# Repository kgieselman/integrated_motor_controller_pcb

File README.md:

# Integrated Motor Controller PCB

A reusable base board for yearly robotics competitions. The base board handles drive, sensing, control, and radio. Per-season expansion is exposed through a small set of discrete headers (AUX, UART, QWIIC I²C, servo), not a single dedicated mechanism connector.

Adapter boards are named after creature parts: **Fang** (ping pong gripper/launcher), with future adapters extending the menagerie.

## Architecture

```
┌──────────────────────────────────────────────────────────────────┐
│                        Base Board                                │
│                                                                  │
│  ┌───────────────────┐  ┌──────────────────────────────────────┐ │
│  │ Power             │  │  STM32 H563RIT6                      │ │
│  │ 2S/3S → 5V ×2     │  │  250 MHz, 2MB / 640KB                │ │
│  │ (aux + main)      │  │  Y1 ASE-25MHz active oscillator      │ │
│  │ 5V → 3.3V LDO     │  │  BZ buzzer, D6–D9 LEDs               │ │
│  │ USB/batt PowerPath|  └────────────┬─────────────────────────┘ │
│  └───────────────────┘               │                           │
│                                      │                           │
│  ┌───────────────────────────────────┼───────────────┐           │
│  │   DRV8874 ×2 Motor Drivers        │               │           │
│  │   ~9A peak each                   │  Encoders ×2  │           │
│  │   IN1/IN2 + IPROPI                │  TIM4 / TIM8  │           │
│  └───────────────────────────────────┴───────────────┘           │
│                                                                  │
│  Connectors (* = DNP, footprint reserved):                       │
│   J1  RCVR    1×4 pin       — ELRS/CRSF RX/TX + 5 V *            │
│   J2  SWD     2×3 pin       — SWDIO/SWCLK/nRST, 3.3 V *          │
│   J3  ENC 0   1×3 pin       — encoder 0 signal, 3.3 V *          │
│   J4  ENC 1   1×3 pin       — encoder 1 signal, 3.3 V *          │
│   J5  UART    1×3 pin       — expansion UART, JST GH 1.25 mm *   │
│   J6  CH0     1×3 pin       — servo 0, +5V_Aux, GND *            │
│   J7  I2C     1×4 pin       — I2C SDA/SCL, JST SH 1.0 mm *       │
│   J8  CH1     1×3 pin       — servo 1, +5V_Aux, GND *            │
│   J9  I2C     1×4 pin       — I2C SDA/SCL (alt), JST SH 1.0 mm * │
│   J10 CH2     1×3 pin       — servo 2, +5V_Aux, GND *            │
│   J11 USB-C   USB 2.0       — debug / VBUS-powered logic         │
│   J12 VMeter  1×2 pin       — +BATT/GND for external voltmeter * │
│   J13 BATT    XT60          — 2S/3S LiPo input *                 │
│   J14 MOT 0   1×2 pin       — motor 0 out, Molex Micro-Fit 3.0 * │
│   J15 MOT 1   1×2 pin       — motor 1 out, Molex Micro-Fit 3.0 * │
│   JP1/JP2     solder jumpers — CRSF RX path (bridged by design)  │
└──────────────────────────────────────────────────────────────────┘
```

## Key Specs

| | |
|---|---|
| **MCU** | STM32H563RIT6 — Cortex-M33 @ 250 MHz, 2 MB flash, 640 KB SRAM, LQFP-64 |
| **Clock** | Y1 ASE-25.000MHZ — Abracon active oscillator, 4-pin SMD 3.2×2.5 mm |
| **Motor drivers** | 2× DRV8874 (PWP-16, HTSSOP) — IN1/IN2 mode (PMODE driven high), IPROPI current sense |
| **IMU** | LSM6DSV (U6) — 6-axis, SPI1 on PB3/PB4/PB5, CS=PC12, INT1=PD2, INT2=PB8; LGA-14 3×2.5 mm |
| **EEPROM** | M24C64 — 64 Kbit, I²C1 on PB6/PB7, WC=PA9 |
| **RC control** | External CRSF/ELRS receiver via J1 (1×4); JP1/JP2 solder jumpers bridged by default |
| **Servo channels** | 3, powered from +5V_Aux buck |
| **Expansion UART** | JST GH 1.25 mm |
| **I2C expansion** | JST SH 1.0 mm, 1×4 |
| **Power input** | 2S/3S LiPo (7.4–12.6 V) via XT60; USB-C VBUS can power logic rails only |
| **Power topology** | SW1 power switch; SI7157DP; 2N7002; AP63205WU bucks (5V_Aux + 5V); AP1117-33 LDO for 3.3 V |
| **Debug** | SWD, MCU RST, MCU BOOT0, USR button, power switch, LEDs, buzzer |
| **Board** | 4-layer FR4 |

## Schematic Hierarchy

```
integrated_motor_controller.kicad_sch (Root)
├── power_regulator_2s_3s.kicad_sch — Battery input, power switch, bucks, LDO, VBAT sense
├── mcu_h563r.kicad_sch             — STM32H563, Y1 active oscillator, bypass, pin assignments, VCAP, SW2/SW3
├── motor_driver_drv8874.kicad_sch  — DRV8874 (instantiated twice: Motor 0 + Motor 1), motor output connectors
├── imu_lsm6dsv.kicad_sch           — LSM6DSV on SPI1
├── eeprom_m24c64.kicad_sch         — M24C64 on I²C1
├── debug_leds.kicad_sch            — Debug LEDs (×4), buzzer, user button, transistor drivers
└── connector_usb.kicad_sch         — USB-C receptacle + USBLC6-2SC6 ESD + CC pulldowns
```

Servo, encoder, UART, I2C, RCVR, and SWD connectors are placed directly on the root sheet.

## Status

- [x] Schematic hierarchy defined
- [x] Sub-schematics created and wired
- [x] PCB layout complete (KiCad 10)
- [x] Gerber / drill files generated (`gerbers/`)
- [x] ERC clean
- [x] DRC clean
- [x] BOM and pick-and-place outputs
- [ ] First board assembled and tested

## Getting Started

1. Clone this repo
2. Open `integrated_motor_controller.kicad_pro` in KiCad 10+
3. Custom symbols are in `libraries/symbols/` — resolved via the committed `sym-lib-table`
4. Custom footprints are in `libraries/footprints/` — resolved via `fp-lib-table`

## Repo Structure

```
integrated_motor_controller-pcb/
├── integrated_motor_controller.kicad_pro              # KiCad project file — open this
├── integrated_motor_controller.kicad_sch              # Root schematic
├── integrated_motor_controller.kicad_pcb              # PCB layout
├── power_regulator_2s_3s.kicad_sch
├── mcu_h563r.kicad_sch
├── motor_driver_drv8874.kicad_sch
├── imu_lsm6dsv.kicad_sch
├── eeprom_m24c64.kicad_sch
├── debug_leds.kicad_sch
├── connector_usb.kicad_sch
├── gerbers/                       # Gerber + drill files (ready for fab)
├── output/
│   ├── integrated_motor_controller.csv                # BOM export
│   └── integrated_motor_controller.net                # Netlist export
├── libraries/
│   ├── symbols/                   # Custom KiCad symbol libraries (.kicad_sym)
│   ├── footprints/                # Custom KiCad footprint libraries (.kicad_mod)
│   └── 3d_models/                 # STEP/WRL 3D models
├── sym-lib-table                  # Symbol library table (committed — paths are relative)
└── fp-lib-table                   # Footprint library table (committed — paths are relative)
```

## License

[CERN Open Hardware Licence Version 2 - Strongly Reciprocal (CERN-OHL-S-2.0)](LICENSE) © 2026 Kyle Gieselman

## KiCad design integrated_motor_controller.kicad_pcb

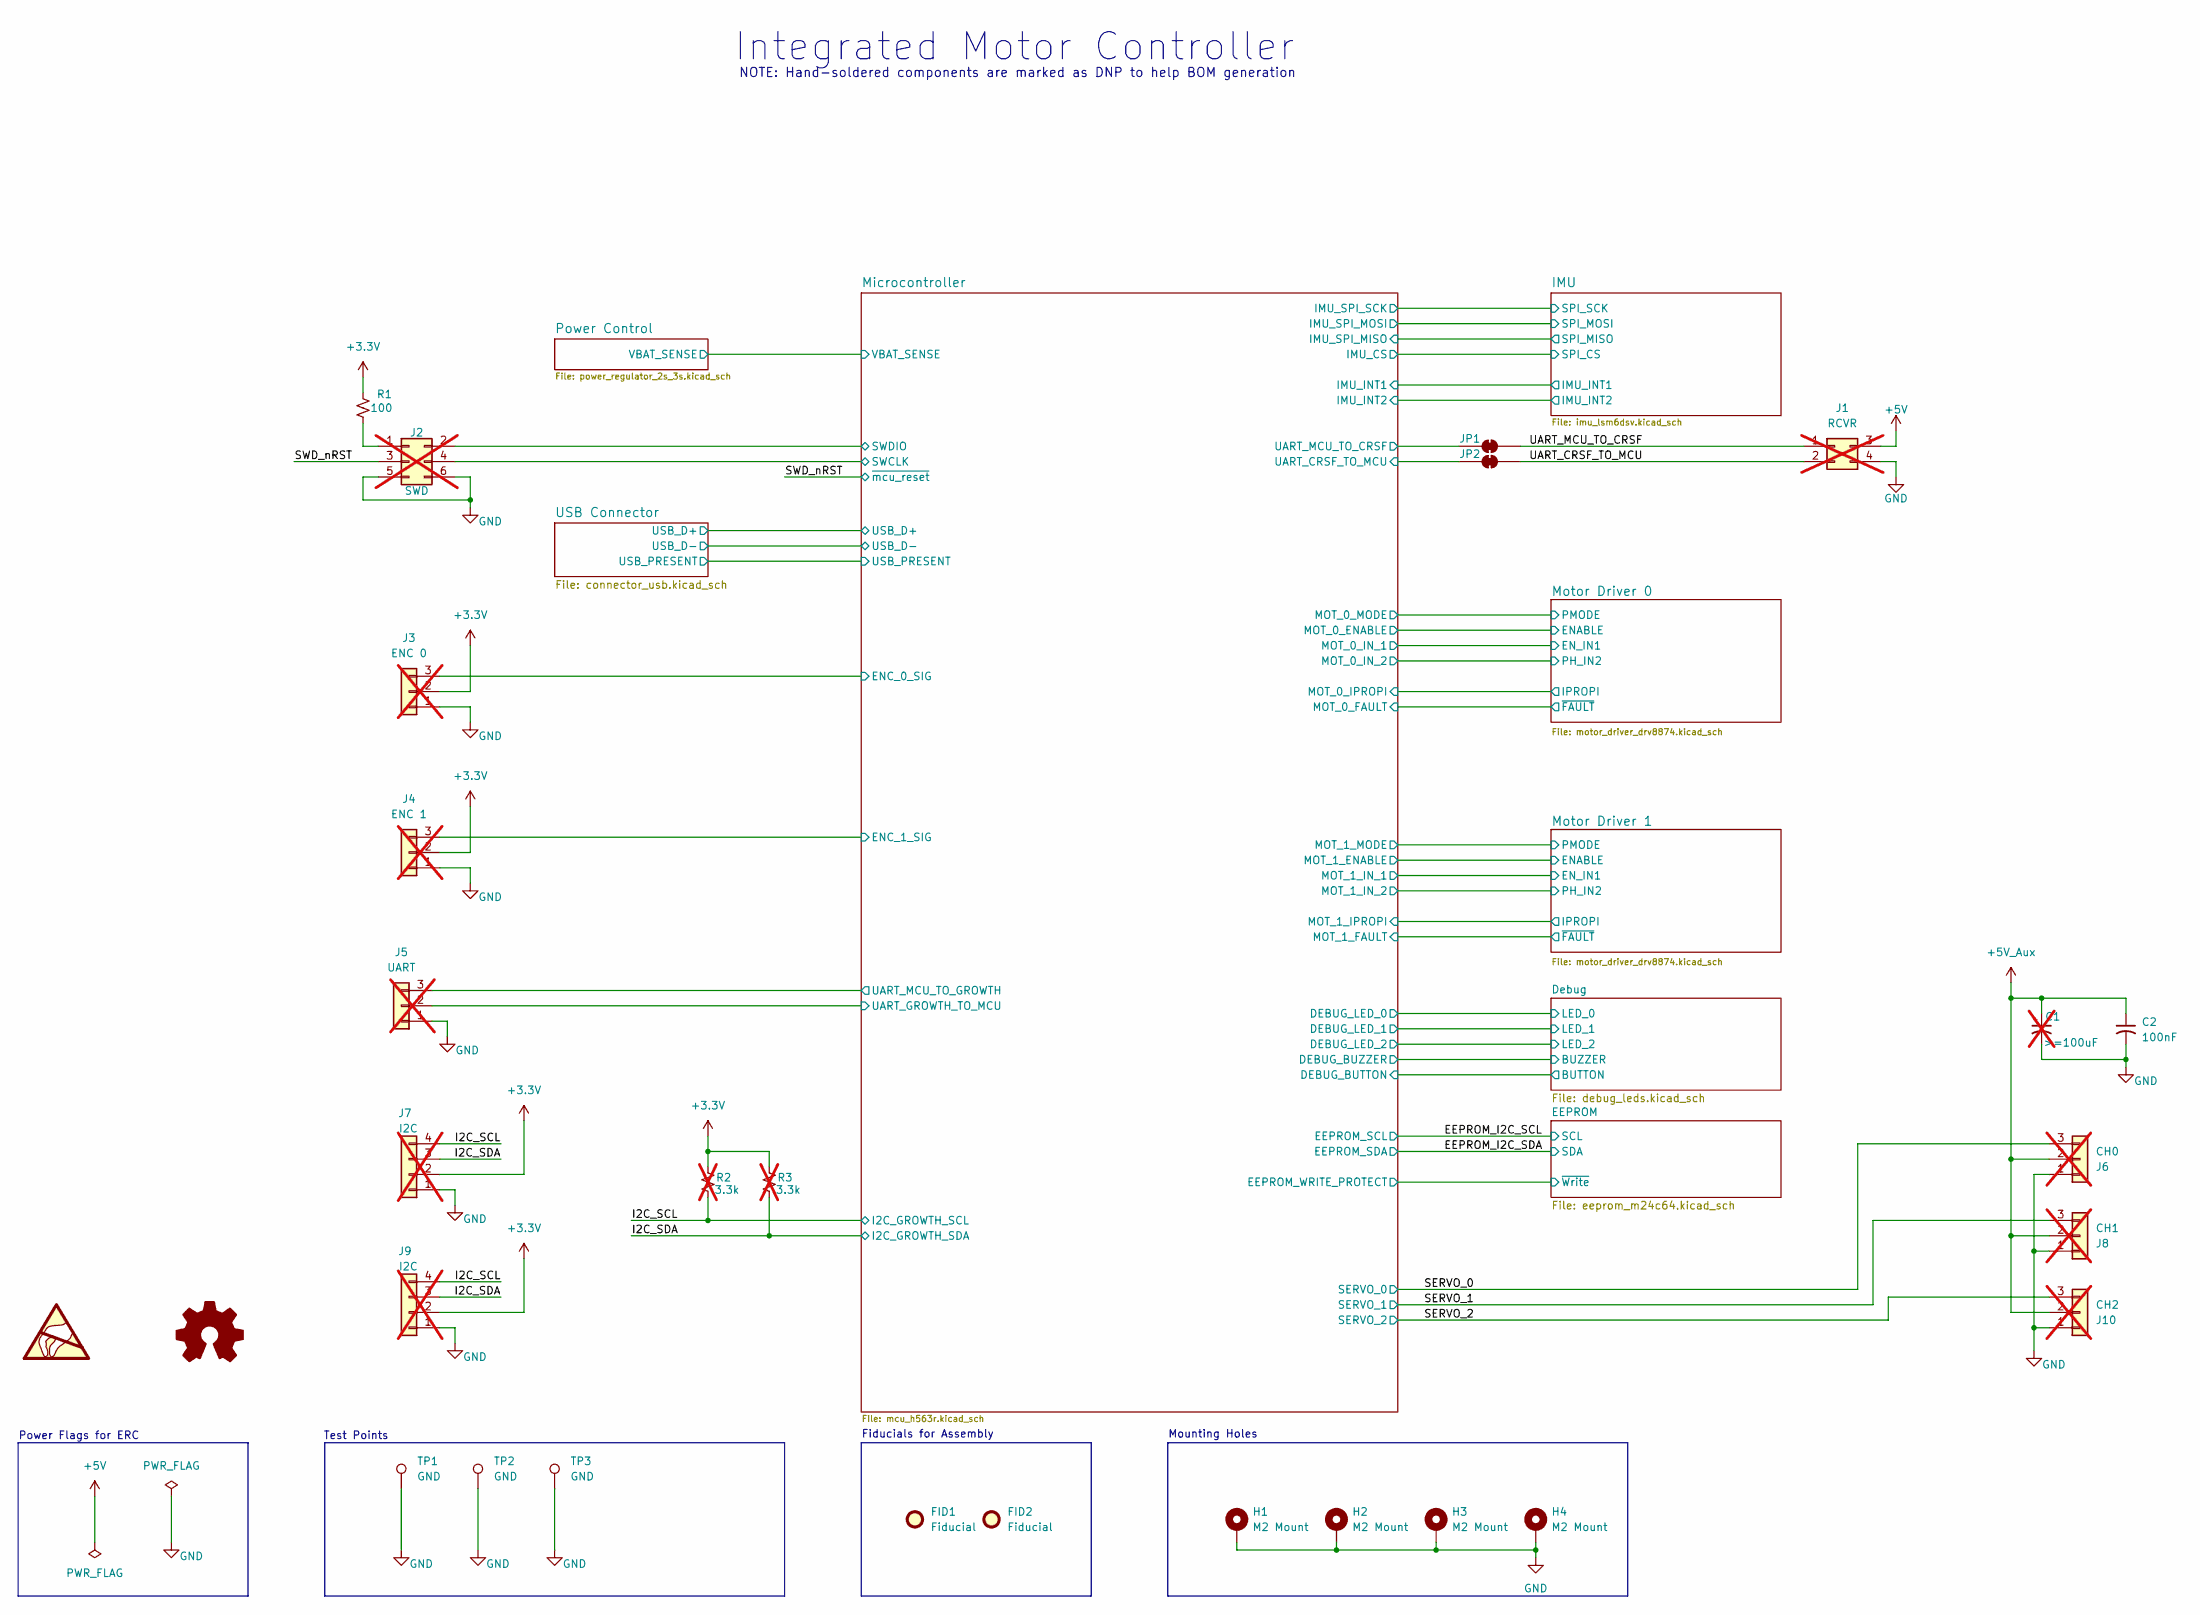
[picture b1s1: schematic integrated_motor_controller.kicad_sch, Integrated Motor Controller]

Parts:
C1: >=100uF; CP_Radial_D5.0mm_P2.00mm; Part No ---; JLCPCB ---; not fitted
C2: 100nF; C_0603_1608Metric; Part No CC0603KRX7R9BB104; JLCPCB C14663
FID1, FID2: Fiducial; ToolingHole_1.152mm; Part No ---; JLCPCB ---
H1, H2, H3, H4: M2 Mount; MountingHole_2.2mm_M2_Pad_Via; Part No ---; JLCPCB ---
J1: RCVR; PinHeader_1x04_P2.54mm_Vertical; Part No ---; JLCPCB ---; not fitted
J2: SWD; PinHeader_2x03_P2.54mm_Vertical; Part No ---; JLCPCB ---; not fitted
J3: ENC 0; PinHeader_1x03_P2.54mm_Vertical; Part No ---; JLCPCB ---; not fitted
J4: ENC 1; PinHeader_1x03_P2.54mm_Vertical; Part No ---; JLCPCB ---; not fitted
J5: UART; JST_GH_BM03B-GHS-TBT_1x03-1MP_P1.25mm_Vertical; Part No TODO; JLCPCB ---; not fitted
J6: CH0; PinHeader_1x03_P2.54mm_Vertical; Part No ----; JLCPCB ----; not fitted
J7, J9: I2C; JST_SH_BM04B-SRSS-TB_1x04-1MP_P1.00mm_Vertical; Part No TODO; JLCPCB ---; not fitted
J8: CH1; PinHeader_1x03_P2.54mm_Vertical; Part No ----; JLCPCB ----; not fitted
J10: CH2; PinHeader_1x03_P2.54mm_Vertical; Part No ----; JLCPCB ----; not fitted
JP1, JP2: SolderJumper_2_Bridged; SolderJumper-2_P1.3mm_Bridged_Pad1.0x1.5mm; Part No ---; JLCPCB ---
R1: 100; R_0603_1608Metric; Part No 0603WAF1000T5E; JLCPCB C22775
R2, R3: 3.3k; R_0603_1608Metric; Part No 0603WAF3301T5E; JLCPCB C22978; not fitted
SYM1: SYM_ESD_Large; ESD-Logo_6.6x6mm_SilkScreen; Part No ---; JLCPCB ---
SYM2: Logo_Open_Hardware_Small; KiCad-Logo2_6mm_SilkScreen; Part No ---; JLCPCB ---
TP1, TP2, TP3: GND; TestPoint_Pad_D1.0mm; Part No ---; JLCPCB ---

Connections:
+5V: J1.3; also elsewhere on the board
+5V_Aux: C1.1, C2.1, J6.2, J8.2, J10.2; also elsewhere on the board
/I2C_SCL: J7.4, J9.4, R2.1; also elsewhere on the board
/I2C_SDA: J7.3, J9.3, R3.1; also elsewhere on the board
/Microcontroller/ENC_0_SIG: J3.3; also elsewhere on the board
/Microcontroller/ENC_1_SIG: J4.3; also elsewhere on the board
/Microcontroller/SWCLK: J2.4; also elsewhere on the board
/Microcontroller/SWDIO: J2.2; also elsewhere on the board
/Microcontroller/UART_CRSF_TO_MCU: JP2.1 (A); also elsewhere on the board
/Microcontroller/UART_GROWTH_TO_MCU: J5.2; also elsewhere on the board
/Microcontroller/UART_MCU_TO_CRSF: JP1.1 (A); also elsewhere on the board
/Microcontroller/UART_MCU_TO_GROWTH: J5.3; also elsewhere on the board
/SERVO_0: J6.3; also elsewhere on the board
/SERVO_1: J8.3; also elsewhere on the board
/SERVO_2: J10.3; also elsewhere on the board
/SWD_nRST: J2.3; also elsewhere on the board
/UART_CRSF_TO_MCU: J1.2, JP2.2 (B)
/UART_MCU_TO_CRSF: J1.1, JP1.2 (B)
unnamed: J2.1, R1.2

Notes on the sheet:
Fiducials for Assembly
Test Points
Integrated Motor Controller
Power Flags for ERC
Mounting Holes
NOTE: Hand-soldered components are marked as DNP to help BOM generation

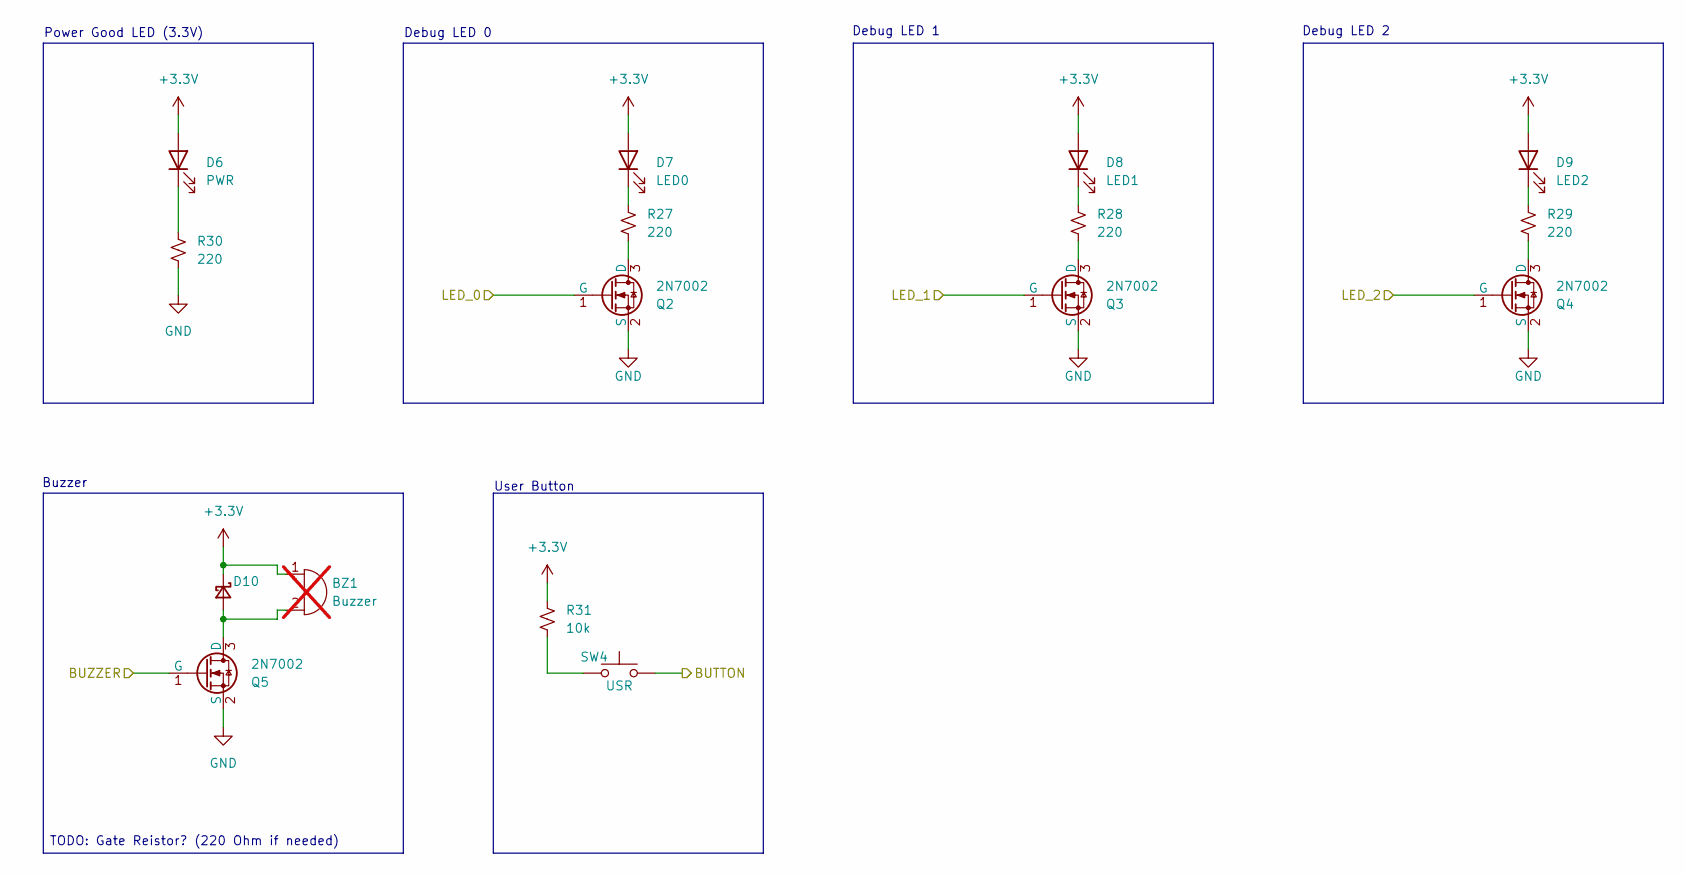
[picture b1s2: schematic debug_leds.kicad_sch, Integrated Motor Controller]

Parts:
BZ1: Buzzer; MagneticBuzzer_PUI_AT-0927-TT-6-R; Part No AT-0927-TT-6-R; JLCPCB ---; not fitted
D6: PWR; LED_0603_1608Metric; Part No KT-0603R; JLCPCB C2286
D7: LED0; LED_0603_1608Metric; Part No KT-0603R; JLCPCB C2286
D8: LED1; LED_0603_1608Metric; Part No KT-0603R; JLCPCB C2286
D9: LED2; LED_0603_1608Metric; Part No KT-0603R; JLCPCB C2286
D10: Schottky; D_SOD-123; Part No B5819W SL; JLCPCB C8598
Q2, Q3, Q4, Q5: 2N7002; SOT-23; Part No 2N7002; JLCPCB C8545
R27, R28, R29, R30: 220; R_0603_1608Metric; Part No 0603WAF2200T5E; JLCPCB C22962
R31: 10k; R_0603_1608Metric; Part No 0603WAF1002T5E; JLCPCB C25804
SW4: USR; SW_SPST_TS-1088-xR020; Part No TS-1088-AR02016; JLCPCB C720477

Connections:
/Debug/BUTTON: SW4.2; also elsewhere on the board
/Debug/BUZZER: Q5.1 (G); also elsewhere on the board
/Debug/LED_0: Q2.1 (G); also elsewhere on the board
/Debug/LED_1: Q3.1 (G); also elsewhere on the board
/Debug/LED_2: Q4.1 (G); also elsewhere on the board
unnamed: BZ1.2 (-), D10.2 (A), Q5.3 (D)
unnamed: D7.1 (K), R27.1
unnamed: D8.1 (K), R28.1
unnamed: Q2.3 (D), R27.2
unnamed: Q3.3 (D), R28.2
unnamed: R31.1, SW4.1

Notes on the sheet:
Debug LED 2
Buzzer
User Button
Debug LED 0
Power Good LED (3.3V)
Debug LED 1
TODO: Gate Reistor? (220 Ohm if needed)

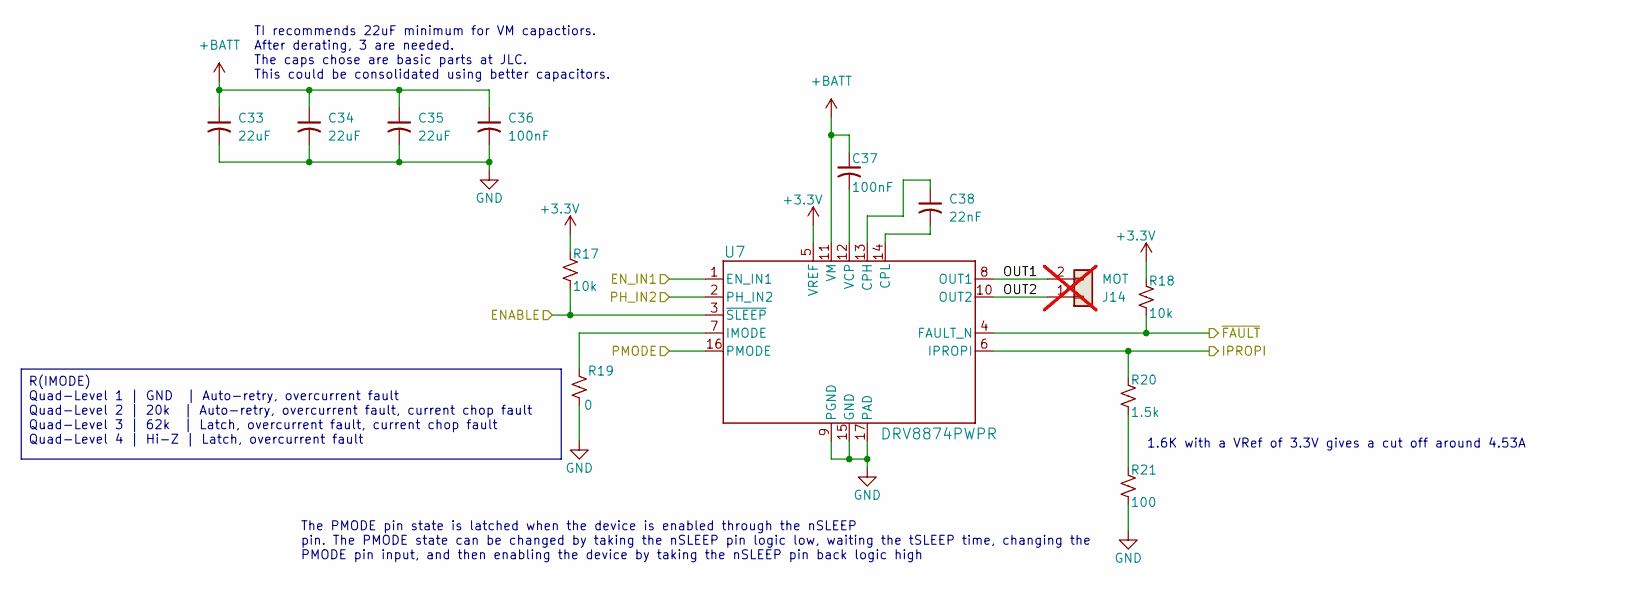
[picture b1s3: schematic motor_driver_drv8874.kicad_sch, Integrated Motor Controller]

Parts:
C33, C34, C35: 22uF; C_1206_3216Metric; Part No CL31A226KAHNNNE; JLCPCB C12891
C36, C37: 100nF; C_0603_1608Metric; Part No CC0603KRX7R9BB104; JLCPCB C14663
C38: 22nF; C_0603_1608Metric; Part No CL10B223KB8NNNC; JLCPCB C21122
J14: MOT; Molex_Micro-Fit_3.0_43650-0215_1x02_P3.00mm_Vertical; Part No 0436500215; JLCPCB ---; not fitted
R17, R18: 10k; R_0603_1608Metric; Part No 0603WAF1002T5E; JLCPCB C25804
R19: 0; R_0805_2012Metric; Part No 0805W8F0000T5E; JLCPCB C17477
R20: 1.5k; R_0805_2012Metric; Part No 0805W8F1501T5E; JLCPCB C4310
R21: 100; R_0805_2012Metric; Part No 0805W8F1000T5E; JLCPCB C17408
U7: DRV8874PWPR; PWP0016J_N; Part No DRV8874PWPR; JLCPCB C1855818

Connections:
+BATT: C33.1, C34.1, C35.1, C36.1, C37.1, U7.11 (VM); also elsewhere on the board
/Microcontroller/MOT_0_ENABLE: R17.1, U7.3 (~SLEEP); also elsewhere on the board
/Microcontroller/MOT_0_FAULT: R18.1, U7.4 (FAULT_N); also elsewhere on the board
/Microcontroller/MOT_0_IN_1: U7.1 (EN_IN1); also elsewhere on the board
/Microcontroller/MOT_0_IN_2: U7.2 (PH_IN2); also elsewhere on the board
/Microcontroller/MOT_0_IPROPI: R20.2, U7.6 (IPROPI); also elsewhere on the board
/Microcontroller/MOT_0_MODE: U7.16 (PMODE); also elsewhere on the board
/Motor Driver 0/OUT1: J14.2, U7.8 (OUT1)
/Motor Driver 0/OUT2: J14.1, U7.10 (OUT2)
unnamed: R20.1, R21.2
unnamed: C38.1, U7.13 (CPH)
unnamed: C38.2, U7.14 (CPL)
unnamed: R19.1, U7.7 (IMODE)
unnamed: C37.2, U7.12 (VCP)

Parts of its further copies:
C39, C40, C41: 22uF; C_1206_3216Metric; Part No CL31A226KAHNNNE; JLCPCB C12891
C42, C43: 100nF; C_0603_1608Metric; Part No CC0603KRX7R9BB104; JLCPCB C14663
C44: 22nF; C_0603_1608Metric; Part No CL10B223KB8NNNC; JLCPCB C21122
J15: MOT; Molex_Micro-Fit_3.0_43650-0215_1x02_P3.00mm_Vertical; Part No 0436500215; JLCPCB ---; not fitted
R22, R23: 10k; R_0603_1608Metric; Part No 0603WAF1002T5E; JLCPCB C25804
R24: 0; R_0805_2012Metric; Part No 0805W8F0000T5E; JLCPCB C17477
R25: 1.5k; R_0805_2012Metric; Part No 0805W8F1501T5E; JLCPCB C4310
R26: 100; R_0805_2012Metric; Part No 0805W8F1000T5E; JLCPCB C17408
U8: DRV8874PWPR; PWP0016J_N; Part No DRV8874PWPR; JLCPCB C1855818

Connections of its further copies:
+BATT: C39.1, C40.1, C41.1, C42.1, C43.1, U8.11 (VM); also elsewhere on the board
/Microcontroller/MOT_1_ENABLE: R22.1, U8.3 (~SLEEP); also elsewhere on the board
/Microcontroller/MOT_1_FAULT: R23.1, U8.4 (FAULT_N); also elsewhere on the board
/Microcontroller/MOT_1_IN_1: U8.1 (EN_IN1); also elsewhere on the board
/Microcontroller/MOT_1_IN_2: U8.2 (PH_IN2); also elsewhere on the board
/Microcontroller/MOT_1_IPROPI: R25.2, U8.6 (IPROPI); also elsewhere on the board
/Microcontroller/MOT_1_MODE: U8.16 (PMODE); also elsewhere on the board
/Motor Driver 1/OUT1: J15.2, U8.8 (OUT1)
/Motor Driver 1/OUT2: J15.1, U8.10 (OUT2)
unnamed: R25.1, R26.2
unnamed: C44.1, U8.13 (CPH)
unnamed: C44.2, U8.14 (CPL)
unnamed: R24.1, U8.7 (IMODE)
unnamed: C43.2, U8.12 (VCP)

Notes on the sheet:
1.6K with a VRef of 3.3V gives a cut off around 4.53A
The PMODE pin state is latched when the device is enabled through the nSLEEP pin. The PMODE state can be changed by taking the nSLEEP pin logic low, waiting the tSLEEP time, changing the PMODE pin input, and then enabling the device by taking the nSLEEP pin back logic high
TI recommends 22uF minimum for VM capactiors. After derating, 3 are needed. The caps chose are basic parts at JLC. This could be consolidated using better capacitors.
R(IMODE) Quad-Level 1 | GND | Auto-retry, overcurrent fault Quad-Level 2 | 20k | Auto-retry, overcurrent fault, current chop fault Quad-Level 3 | 62k | Latch, overcurrent fault, current chop fault Quad-Level 4 | Hi-Z | Latch, overcurrent fault

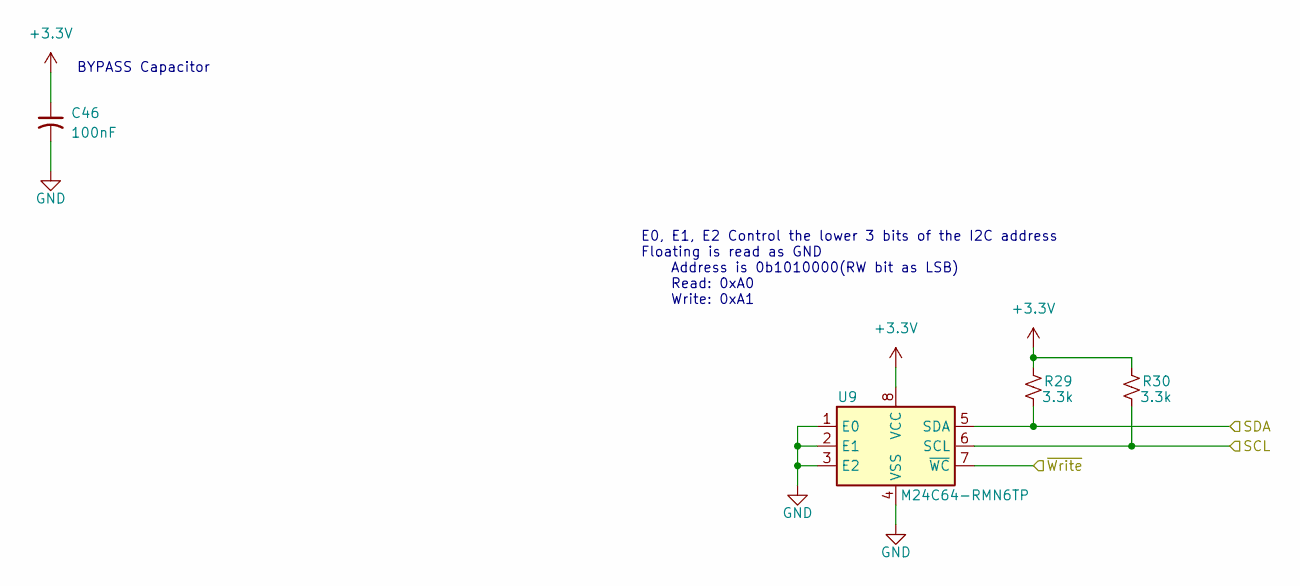
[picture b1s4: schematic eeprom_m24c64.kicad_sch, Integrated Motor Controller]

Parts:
C46: 100nF; C_0603_1608Metric; Part No CC0603KRX7R9BB104; JLCPCB C14663
R29, R30: 3.3k; R_0603_1608Metric; Part No 0603WAF3301T5E; JLCPCB C22978
U9: M24C64-RMN6TP; SOIC-8_3.9x4.9mm_P1.27mm; Part No M24C64-RMN6TP; JLCPCB C79988

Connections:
/EEPROM/~Write: U9.7 (~WC); also elsewhere on the board

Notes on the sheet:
E0, E1, E2 Control the lower 3 bits of the I2C address Floating is read as GND Address is 0b1010000(RW bit as LSB) Read: 0xA0 Write: 0xA1
BYPASS Capacitor

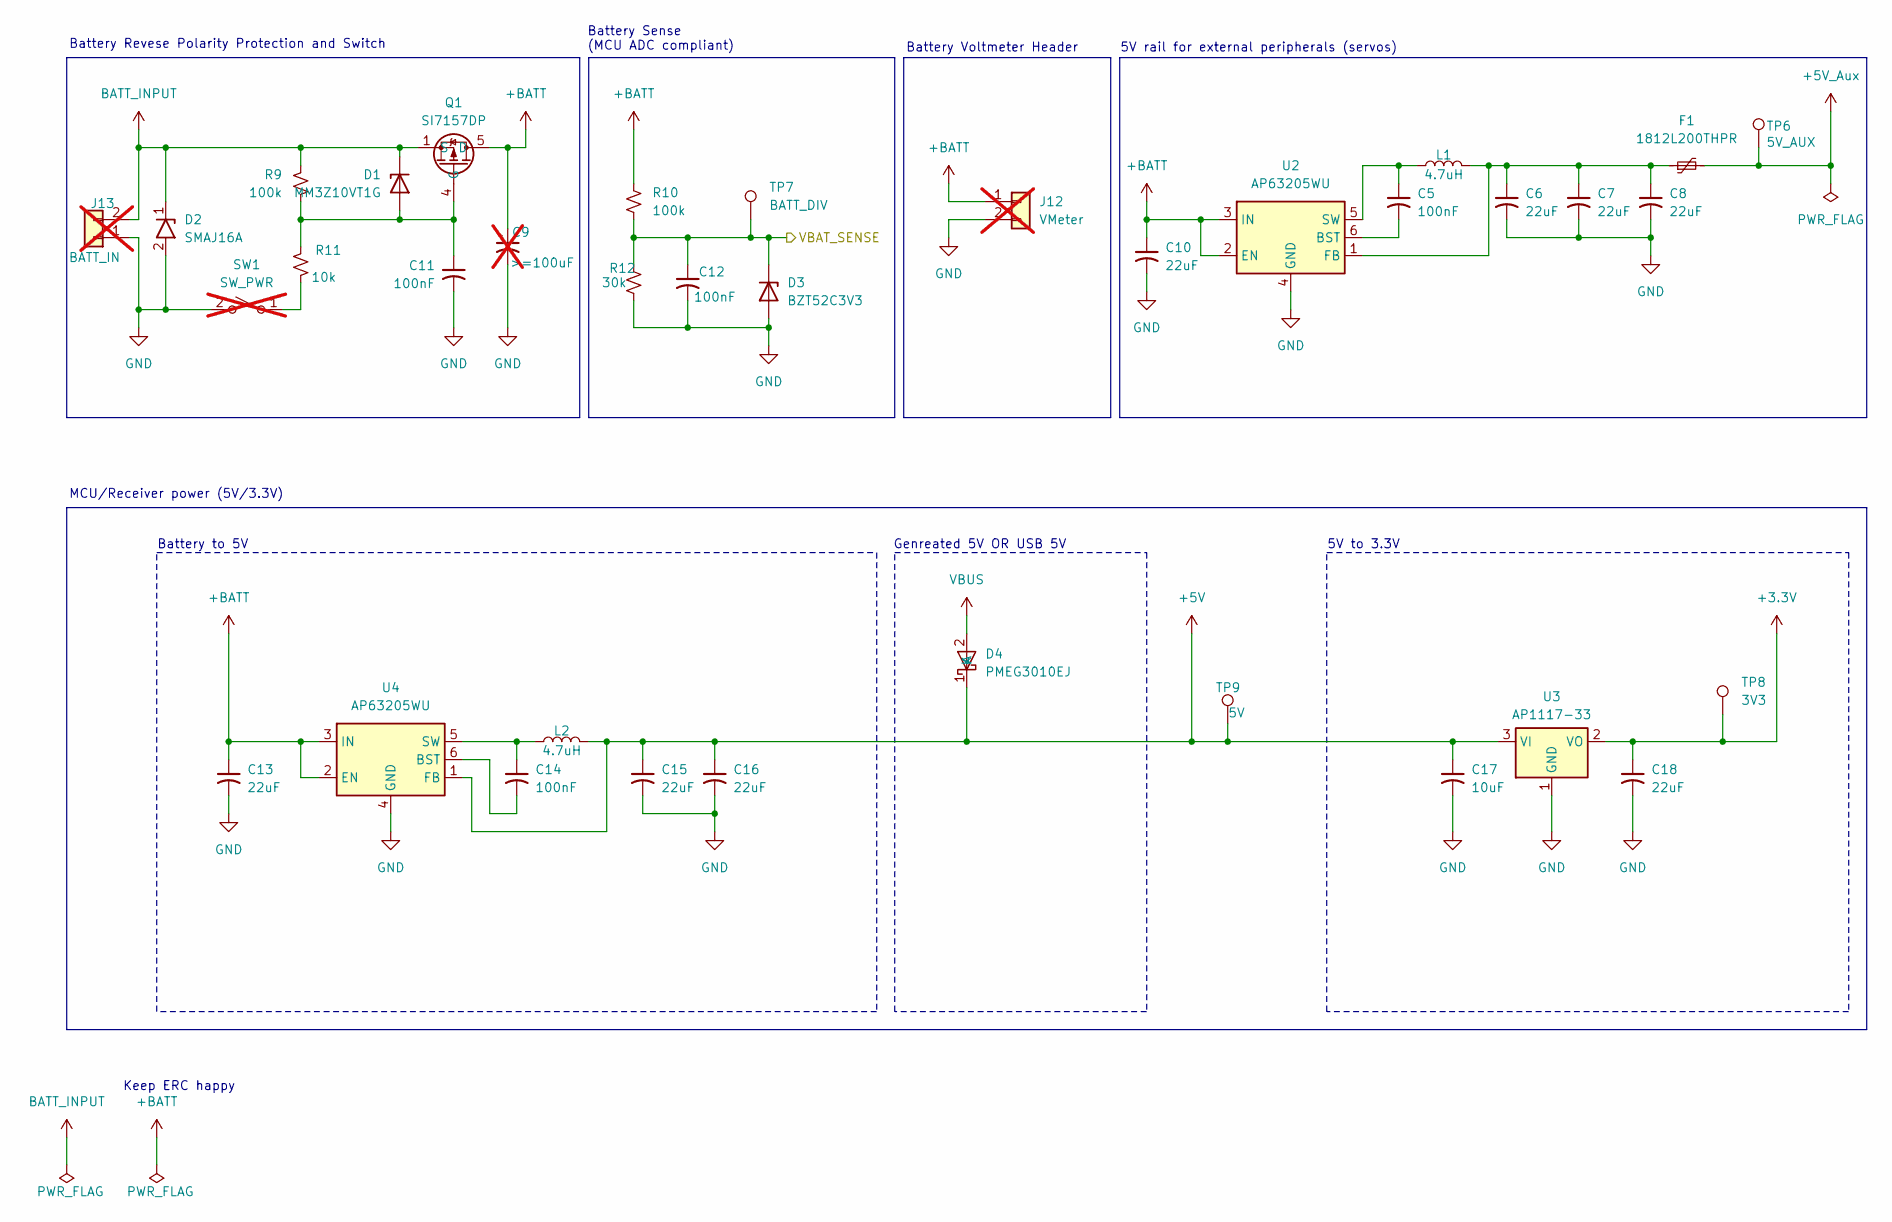
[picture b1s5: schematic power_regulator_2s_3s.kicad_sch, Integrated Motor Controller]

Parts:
C5, C11, C12, C14: 100nF; C_0603_1608Metric; Part No CC0603KRX7R9BB104; JLCPCB C14663
C6, C7, C8, C10, C13, C15, C16, C18: 22uF; C_1206_3216Metric; Part No CL31A226KAHNNNE; JLCPCB C12891
C9: >=100uF; CP_Radial_D5.0mm_P2.00mm; Part No ---; JLCPCB ---; not fitted
C17: 10uF; C_0603_1608Metric; Part No CL10A106MA8NRNC; JLCPCB C96446
D1: MM3Z10VT1G; D_SOD-323; Part No MM3Z10VT1G; JLCPCB C39057
D2: SMAJ16A; D_SMA; Part No SMAJ16A; JLCPCB C74561
D3: BZT52C3V3; D_SOD-123; Part No BZT52C3V3-7-F; JLCPCB C151564
D4: PMEG3010EJ; D_SOD-323F; Part No PMEG3010EJ,115; JLCPCB C255586
F1: 1812L200THPR; Fuse_1812_4532Metric; Part No 1812L200THPR; JLCPCB C207074
J12: VMeter; PinHeader_1x02_P2.54mm_Vertical; Part No ---; JLCPCB ---; not fitted
J13: BATT_IN; AMASS_XT60-M_1x02_P7.20mm_Vertical; Part No ---; JLCPCB ---; not fitted
L1, L2: 4.7uH; L_Sunlord_MWSA0503S; Part No MWSA0503S-4R7MT; JLCPCB C408410
Q1: SI7157DP; PowerPAK_SO-8_Single; Part No SI7157DP-T1-GE3; JLCPCB C3279562
R9, R10: 100k; R_0603_1608Metric; Part No 0603WAF1003T5E; JLCPCB C25803
R11: 10k; R_0603_1608Metric; Part No 0603WAF1002T5E; JLCPCB C25804
R12: 30k; R_0603_1608Metric; Part No 0603WAF3002T5E; JLCPCB C22984
SW1: SW_PWR; PinHeader_1x02_P2.54mm_Vertical; Part No ---; JLCPCB ---; not fitted
TP6: 5V_AUX; TestPoint_Pad_D1.0mm; Part No ---; JLCPCB ---
TP7: BATT_DIV; TestPoint_Pad_D1.0mm; Part No ---; JLCPCB ---
TP8: 3V3; TestPoint_Pad_D1.0mm; Part No ---; JLCPCB ---
TP9: 5V; TestPoint_Pad_D1.0mm; Part No ---; JLCPCB ---
U2, U4: AP63205WU; TSOT-23-6; Part No AP63205WU-7; JLCPCB C2071056
U3: AP1117-33; SOT-223-3_TabPin2; Part No AMS1117-3.3; JLCPCB C6186

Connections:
+5V: C15.1, C16.1, C17.1, D4.1 (K), L2.2, TP9.1 (1_1), U3.3 (VI), U4.1 (FB); also elsewhere on the board
+5V_Aux: F1.2, TP6.1 (1_1); also elsewhere on the board
+BATT: C9.1, C10.1, C13.1, J12.1, Q1.5 (D), R10.1, U2.2 (EN), U2.3 (IN), U4.2 (EN), U4.3 (IN); also elsewhere on the board
/Microcontroller/VBAT_SENSE: C12.1, D3.1 (K), R10.2, R12.1, TP7.1 (1_1); also elsewhere on the board
BATT_INPUT: D1.1 (K), D2.1 (A1), J13.2, Q1.1 (S), Q1.2 (S), Q1.3 (S), R9.2
unnamed: C11.1, D1.2 (A), Q1.4 (G), R9.1, R11.2
unnamed: R11.1, SW1.1 (A)
unnamed: C5.2, U2.6 (BST)
unnamed: C6.1, C7.1, C8.1, F1.1, L1.2, U2.1 (FB)
unnamed: C5.1, L1.1, U2.5 (SW)
unnamed: C14.2, U4.6 (BST)
unnamed: C14.1, L2.1, U4.5 (SW)
VBUS: D4.2 (A); also elsewhere on the board

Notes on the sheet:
Battery to 5V
Battery Sense (MCU ADC compliant)
Battery Revese Polarity Protection and Switch
Battery Voltmeter Header
5V to 3.3V
MCU/Receiver power (5V/3.3V)
Keep ERC happy
Genreated 5V OR USB 5V
5V rail for external peripherals (servos)

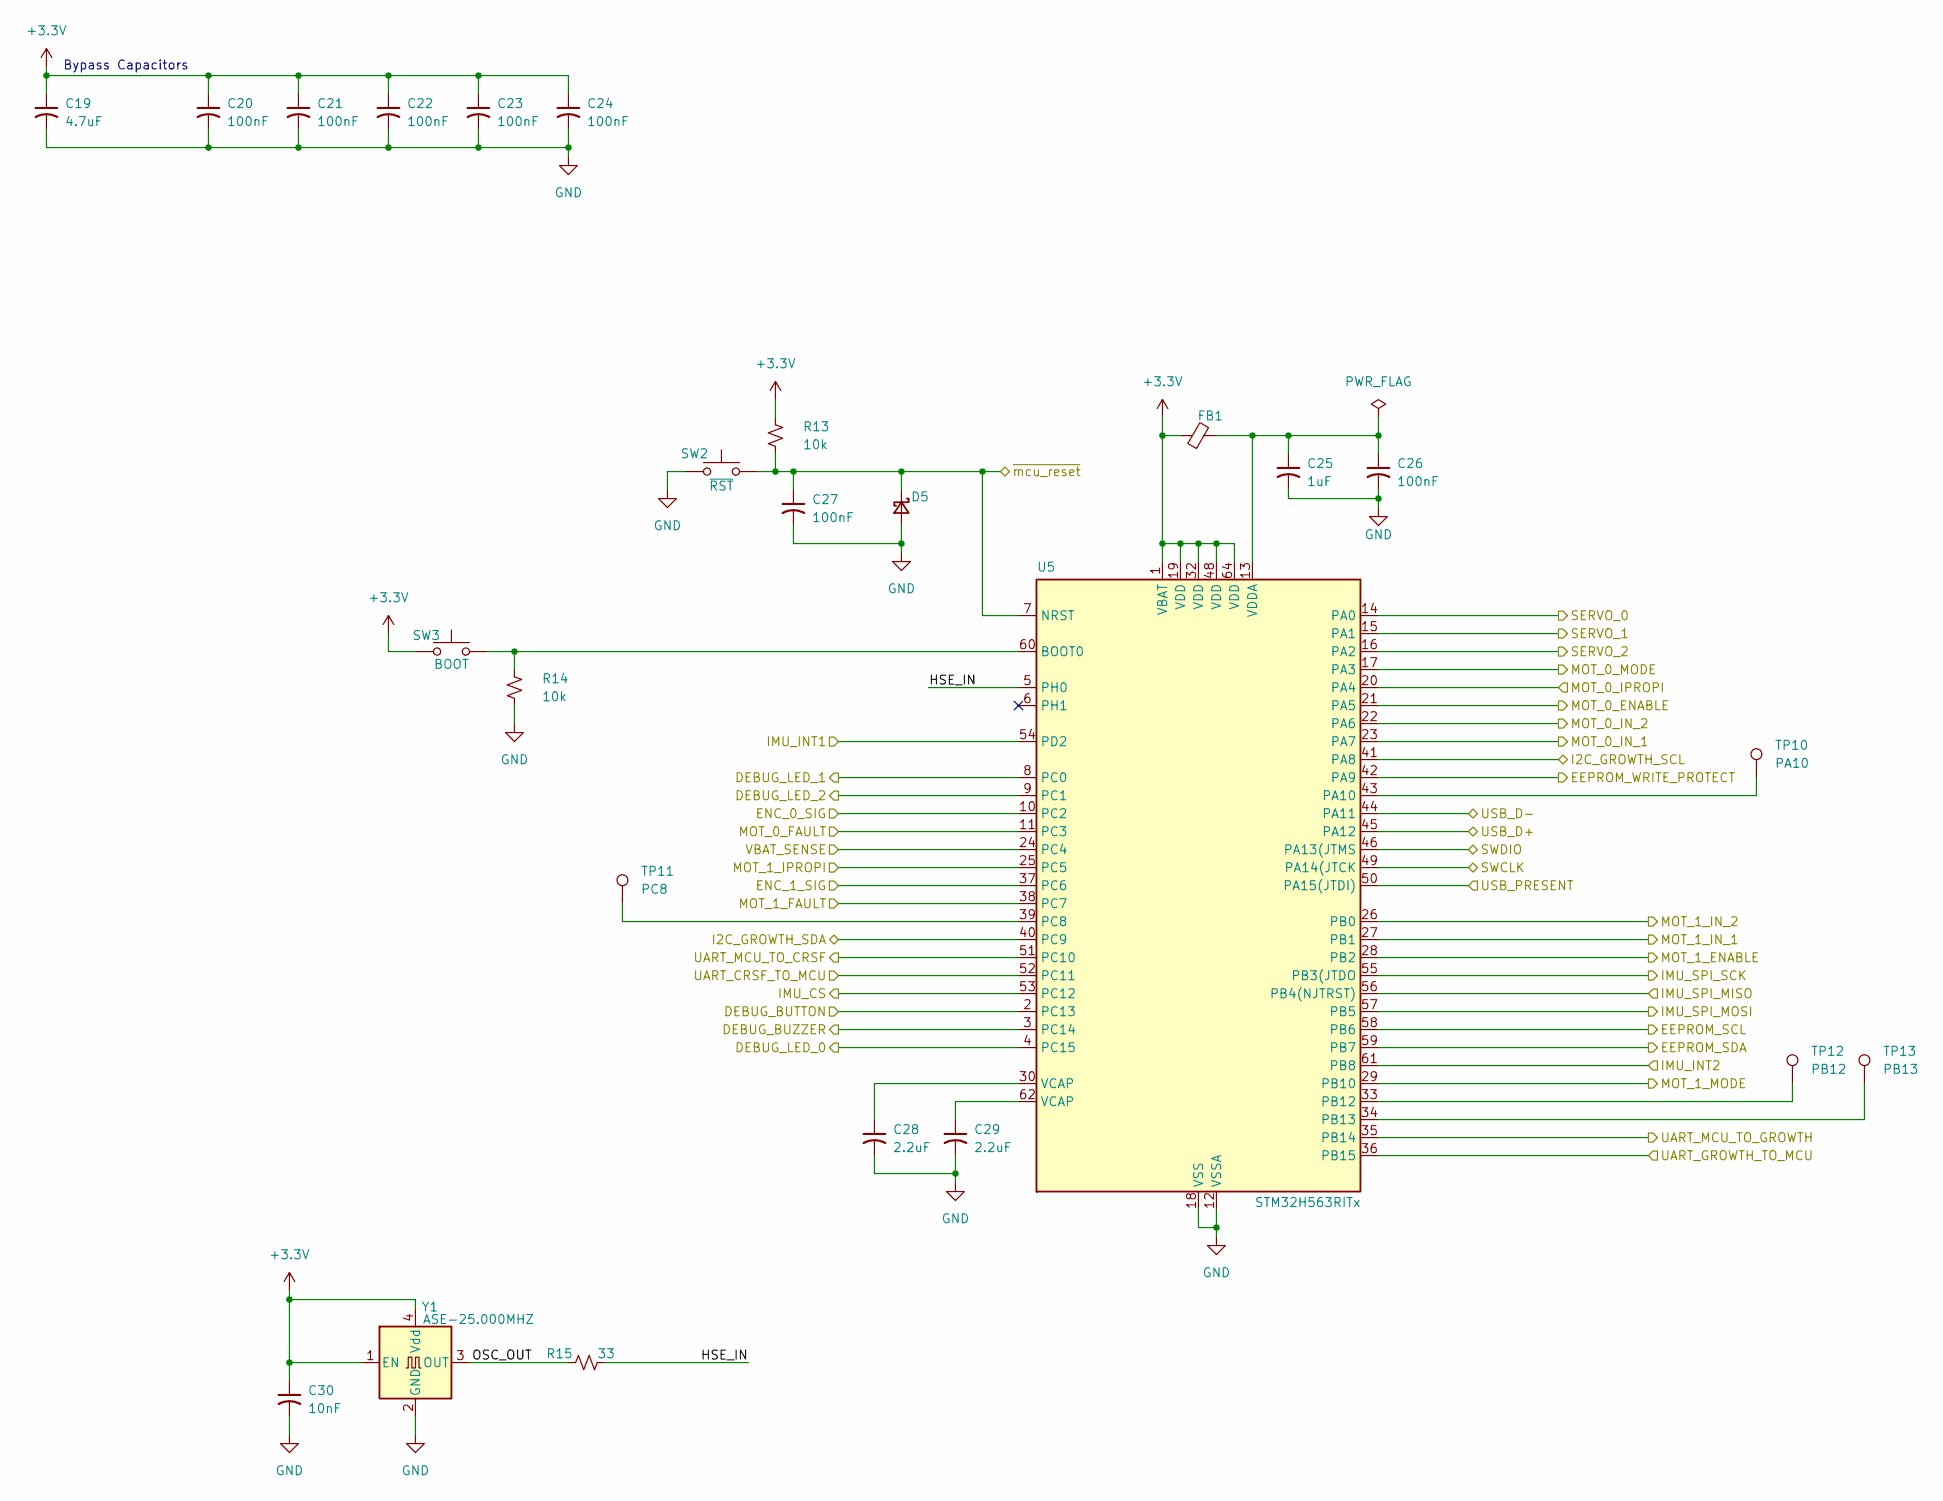
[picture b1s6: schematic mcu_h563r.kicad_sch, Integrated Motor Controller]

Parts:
C19: 4.7uF; C_0603_1608Metric; Part No CL10A475KO8NNNC; JLCPCB C19666
C20, C21, C22, C23, C24, C26, C27: 100nF; C_0603_1608Metric; Part No CC0603KRX7R9BB104; JLCPCB C14663
C25: 1uF; C_0603_1608Metric; Part No CL10A105KB8NNNC; JLCPCB C15849
C28, C29: 2.2uF; C_0603_1608Metric; Part No CL10A225KO8NNNC; JLCPCB C23630
C30: 10nF; C_0603_1608Metric; Part No 0603B103K500NT; JLCPCB C57112
D5: Schottky; D_SOD-123; Part No B5819W SL; JLCPCB C8598
FB1: Ferrite; L_0805_2012Metric; Part No GZ2012D601TF; JLCPCB C1017
R13, R14: 10k; R_0603_1608Metric; Part No 0603WAF1002T5E; JLCPCB C25804
R15: 33; R_0603_1608Metric; Part No 0603WAF330JT5E; JLCPCB C23140
SW2: ~{RST}; SW_SPST_TS-1088-xR020; Part No TS-1088-AR02016; JLCPCB C720477
SW3: BOOT; SW_SPST_TS-1088-xR020; Part No TS-1088-AR02016; JLCPCB C720477
TP10: PA10; TestPoint_Pad_D1.0mm; Part No ---; JLCPCB ---
TP11: PC8; TestPoint_Pad_D1.0mm; Part No ---; JLCPCB ---
TP12: PB12; TestPoint_Pad_D1.0mm; Part No ---; JLCPCB ---
TP13: PB13; TestPoint_Pad_D1.0mm; Part No ---; JLCPCB ---
U5: STM32H563RITx; LQFP-64_10x10mm_P0.5mm; Part No STM32H563RIT6; JLCPCB C20619634
Y1: ASE-25.000MHZ; Oscillator_SMD_Abracon_ASE-4Pin_3.2x2.5mm; Part No ASE-25.000MHZ-L-R-T; JLCPCB C596952

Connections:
/Debug/BUTTON: U5.2 (PC13); also elsewhere on the board
/Debug/BUZZER: U5.3 (PC14); also elsewhere on the board
/Debug/LED_0: U5.4 (PC15); also elsewhere on the board
/Debug/LED_1: U5.8 (PC0); also elsewhere on the board
/Debug/LED_2: U5.9 (PC1); also elsewhere on the board
/EEPROM/~Write: U5.42 (PA9); also elsewhere on the board
/I2C_SCL: U5.41 (PA8); also elsewhere on the board
/I2C_SDA: U5.40 (PC9); also elsewhere on the board
/IMU/IMU_INT1: U5.54 (PD2); also elsewhere on the board
/IMU/IMU_INT2: U5.61 (PB8); also elsewhere on the board
/IMU/SPI_CS: U5.53 (PC12); also elsewhere on the board
/IMU/SPI_MISO: U5.56 (PB4(NJTRST)); also elsewhere on the board
/IMU/SPI_MOSI: U5.57 (PB5); also elsewhere on the board
/IMU/SPI_SCK: U5.55 (PB3(JTDO); also elsewhere on the board
/Microcontroller/ENC_0_SIG: U5.10 (PC2); also elsewhere on the board
/Microcontroller/ENC_1_SIG: U5.37 (PC6); also elsewhere on the board
/Microcontroller/HSE_IN: R15.2, U5.5 (PH0)
/Microcontroller/MOT_0_ENABLE: U5.21 (PA5); also elsewhere on the board
/Microcontroller/MOT_0_FAULT: U5.11 (PC3); also elsewhere on the board
/Microcontroller/MOT_0_IN_1: U5.23 (PA7); also elsewhere on the board
/Microcontroller/MOT_0_IN_2: U5.22 (PA6); also elsewhere on the board
/Microcontroller/MOT_0_IPROPI: U5.20 (PA4); also elsewhere on the board
/Microcontroller/MOT_0_MODE: U5.17 (PA3); also elsewhere on the board
/Microcontroller/MOT_1_ENABLE: U5.28 (PB2); also elsewhere on the board
/Microcontroller/MOT_1_FAULT: U5.38 (PC7); also elsewhere on the board
/Microcontroller/MOT_1_IN_1: U5.27 (PB1); also elsewhere on the board
/Microcontroller/MOT_1_IN_2: U5.26 (PB0); also elsewhere on the board
/Microcontroller/MOT_1_IPROPI: U5.25 (PC5); also elsewhere on the board
/Microcontroller/MOT_1_MODE: U5.29 (PB10); also elsewhere on the board
/Microcontroller/OSC_OUT: R15.1, Y1.3 (OUT)
/Microcontroller/SWCLK: U5.49 (PA14(JTCK); also elsewhere on the board
/Microcontroller/SWDIO: U5.46 (PA13(JTMS); also elsewhere on the board
/Microcontroller/UART_CRSF_TO_MCU: U5.52 (PC11); also elsewhere on the board
/Microcontroller/UART_GROWTH_TO_MCU: U5.36 (PB15); also elsewhere on the board
/Microcontroller/UART_MCU_TO_CRSF: U5.51 (PC10); also elsewhere on the board
/Microcontroller/UART_MCU_TO_GROWTH: U5.35 (PB14); also elsewhere on the board
/Microcontroller/USB_D+: U5.45 (PA12); also elsewhere on the board
/Microcontroller/USB_D-: U5.44 (PA11); also elsewhere on the board
/Microcontroller/USB_PRESENT: U5.50 (PA15(JTDI)); also elsewhere on the board
/Microcontroller/VBAT_SENSE: U5.24 (PC4); also elsewhere on the board
/SERVO_0: U5.14 (PA0); also elsewhere on the board
/SERVO_1: U5.15 (PA1); also elsewhere on the board
/SERVO_2: U5.16 (PA2); also elsewhere on the board
/SWD_nRST: C27.1, D5.1 (K), R13.2, SW2.2, U5.7 (NRST); also elsewhere on the board
unnamed: C28.1, U5.30 (VCAP)
unnamed: C29.1, U5.62 (VCAP)
unnamed: R14.1, SW3.2, U5.60 (BOOT0)
unnamed: TP10.1 (1_1), U5.43 (PA10)
unnamed: TP12.1 (1_1), U5.33 (PB12)
unnamed: TP13.1 (1_1), U5.34 (PB13)
unnamed: TP11.1 (1_1), U5.39 (PC8)
unnamed: C25.1, C26.1, FB1.2, U5.13 (VDDA)

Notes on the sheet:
Bypass Capacitors
